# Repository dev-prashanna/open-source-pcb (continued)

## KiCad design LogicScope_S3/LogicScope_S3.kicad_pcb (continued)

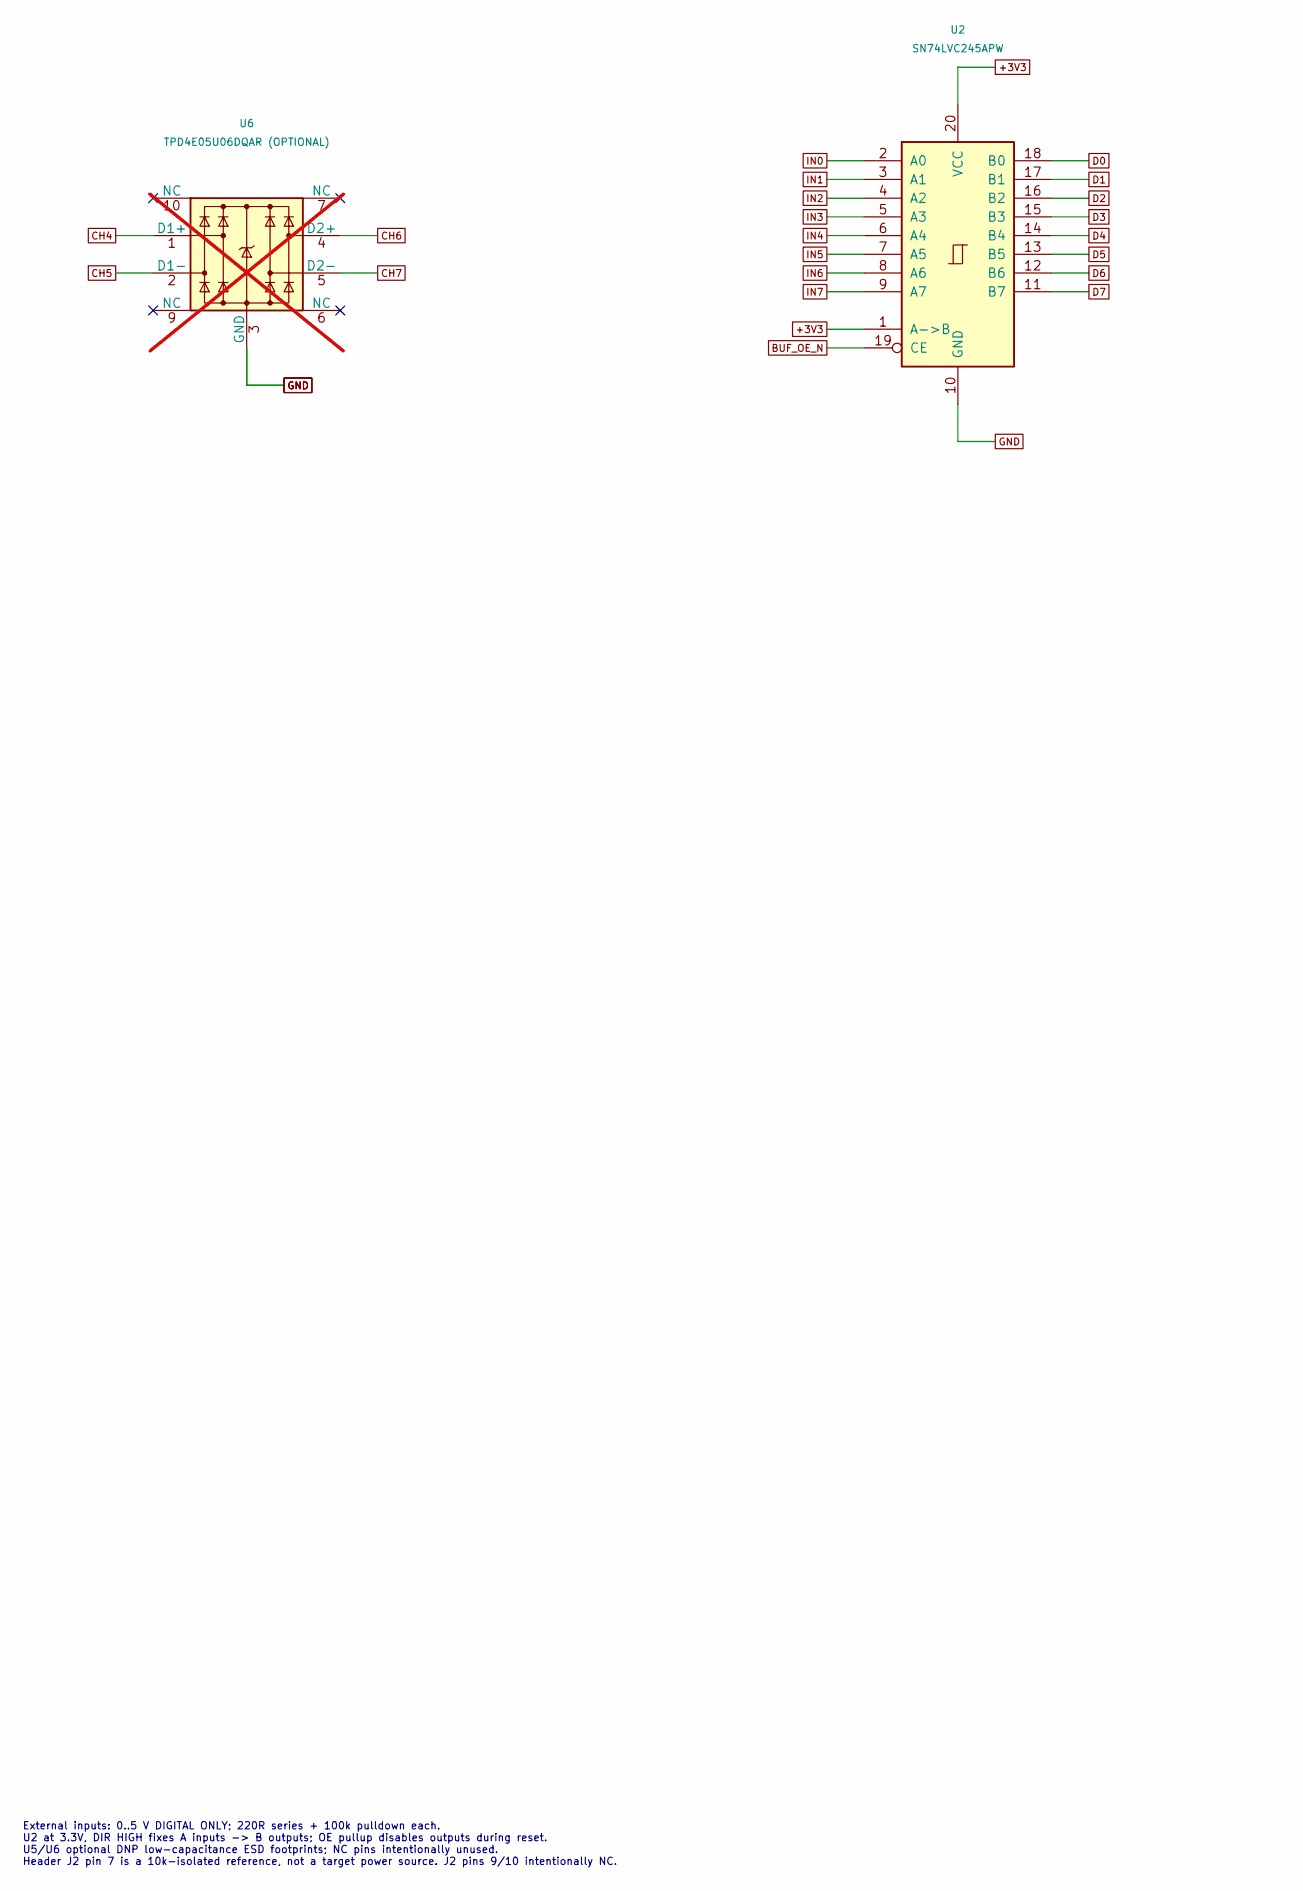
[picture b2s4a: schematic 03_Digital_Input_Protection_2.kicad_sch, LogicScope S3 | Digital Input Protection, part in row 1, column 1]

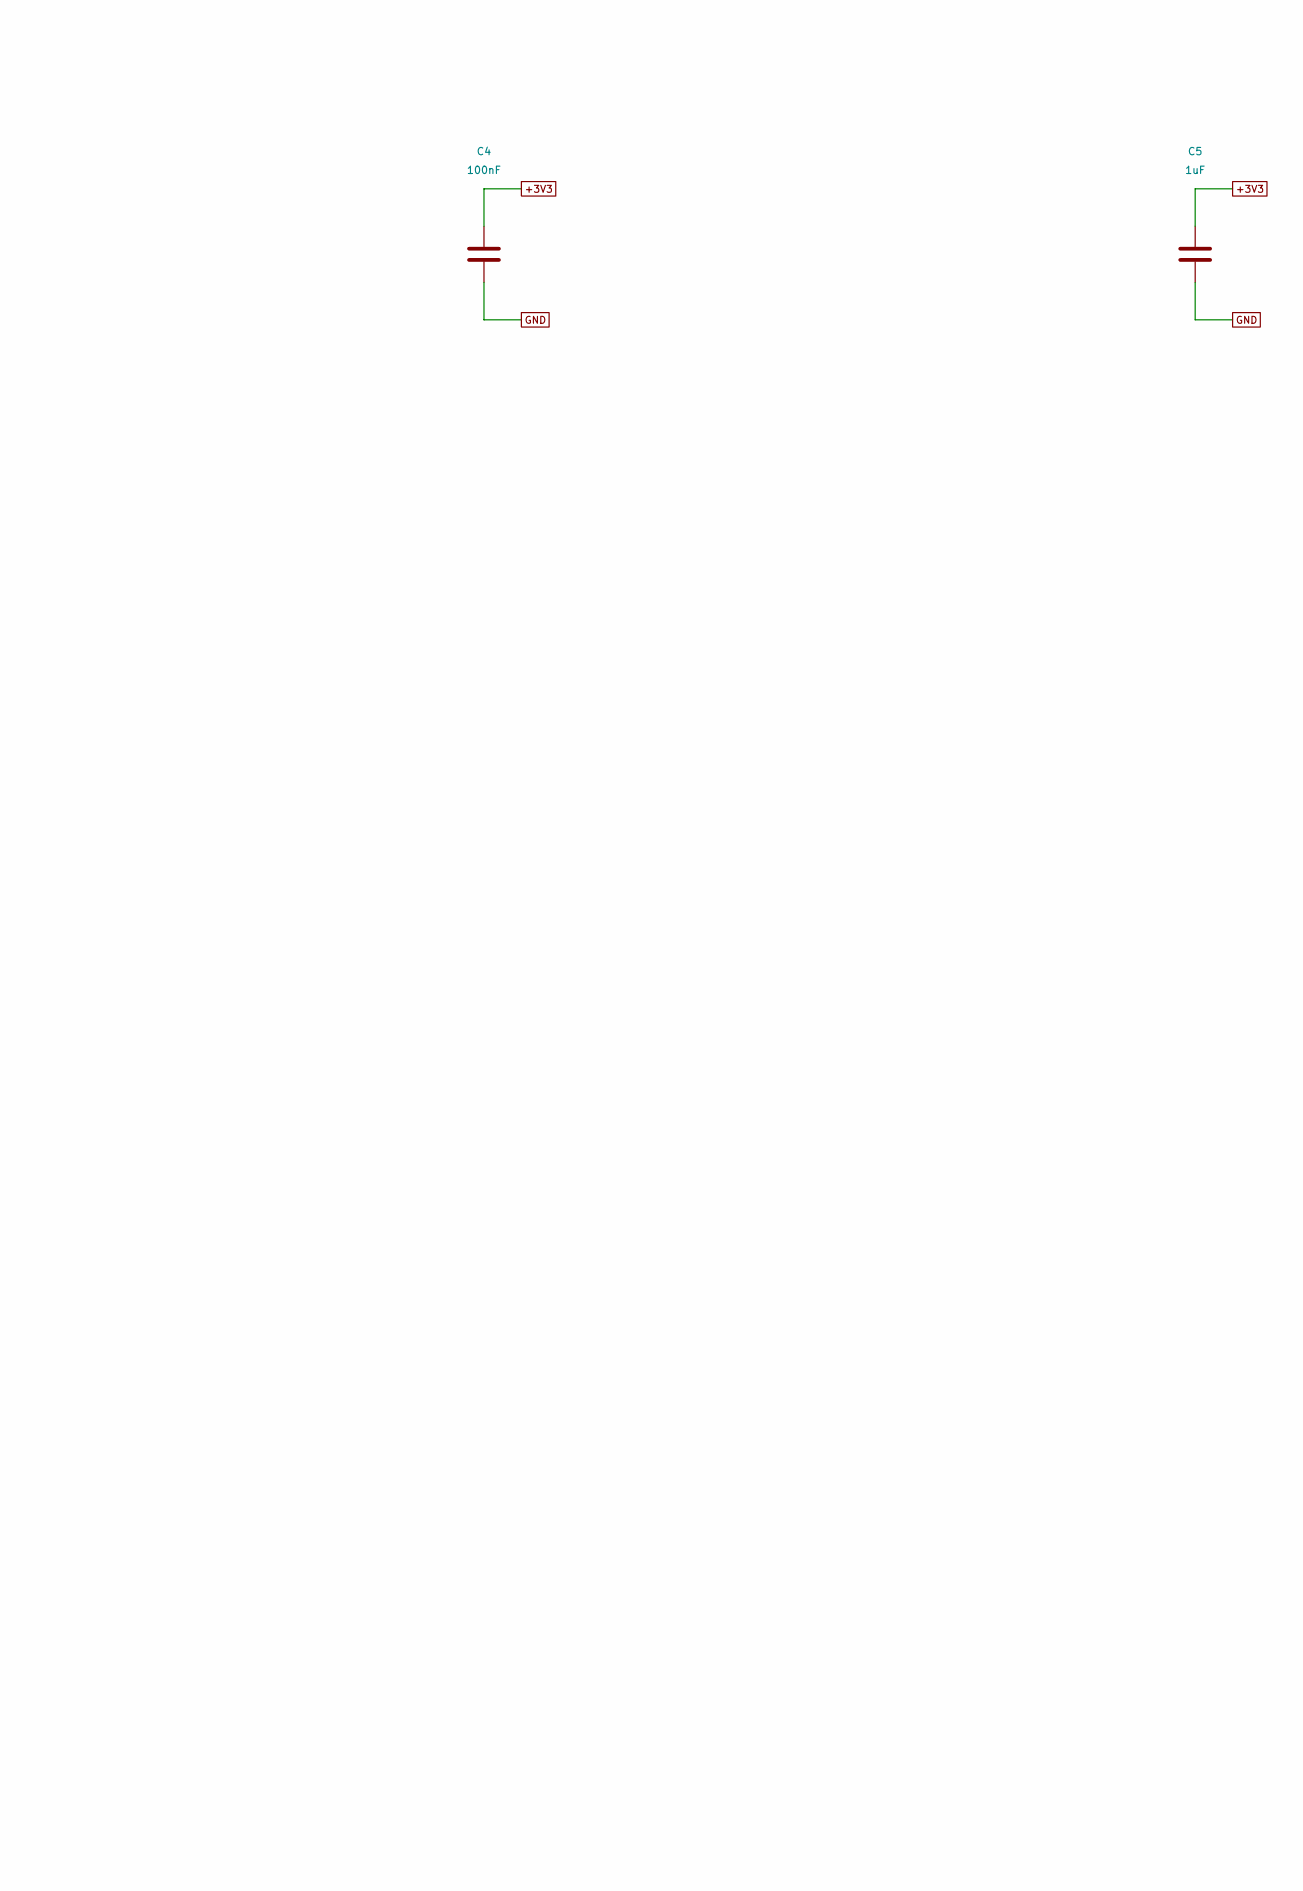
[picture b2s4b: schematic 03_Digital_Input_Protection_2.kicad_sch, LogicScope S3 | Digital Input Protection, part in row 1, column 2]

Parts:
C4: 100nF; C_0603_1608Metric; MPN GRM188R71C104KA01D
C5: 1uF; C_0603_1608Metric; MPN GRM188R61A105KA61D
U2: SN74LVC245APW; TSSOP-20_4.4x6.5mm_P0.65mm; MPN SN74LVC245APW
U6: TPD4E05U06DQAR (OPTIONAL); USON-10_2.5x1.0mm_P0.5mm; MPN TPD4E05U06DQAR; not fitted

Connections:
+3V3: C4.1, C5.1, U2.1 (A->B), U2.20 (VCC); also elsewhere on the board
BUF_OE_N: U2.19 (CE); also elsewhere on the board
CH4: U6.1 (D1+); also elsewhere on the board
CH5: U6.2 (D1-); also elsewhere on the board
CH6: U6.4 (D2+); also elsewhere on the board
CH7: U6.5 (D2-); also elsewhere on the board
D0: U2.18 (B0); also elsewhere on the board
D1: U2.17 (B1); also elsewhere on the board
D2: U2.16 (B2); also elsewhere on the board
D3: U2.15 (B3); also elsewhere on the board
D4: U2.14 (B4); also elsewhere on the board
D5: U2.13 (B5); also elsewhere on the board
D6: U2.12 (B6); also elsewhere on the board
D7: U2.11 (B7); also elsewhere on the board
GND: C4.2, C5.2, U2.10 (GND), U6.3 (GND), U6.8 (GND); also elsewhere on the board
IN0: U2.2 (A0); also elsewhere on the board
IN1: U2.3 (A1); also elsewhere on the board
IN2: U2.4 (A2); also elsewhere on the board
IN3: U2.5 (A3); also elsewhere on the board
IN4: U2.6 (A4); also elsewhere on the board
IN5: U2.7 (A5); also elsewhere on the board
IN6: U2.8 (A6); also elsewhere on the board
IN7: U2.9 (A7); also elsewhere on the board

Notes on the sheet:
External inputs: 0..5 V DIGITAL ONLY; 220R series + 100k pulldown each. U2 at 3.3V, DIR HIGH fixes A inputs -> B outputs; OE pullup disables outputs during reset. U5/U6 optional DNP low-capacitance ESD footprints; NC pins intentionally unused. Header J2 pin 7 is a 10k-isolated reference, not a targ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

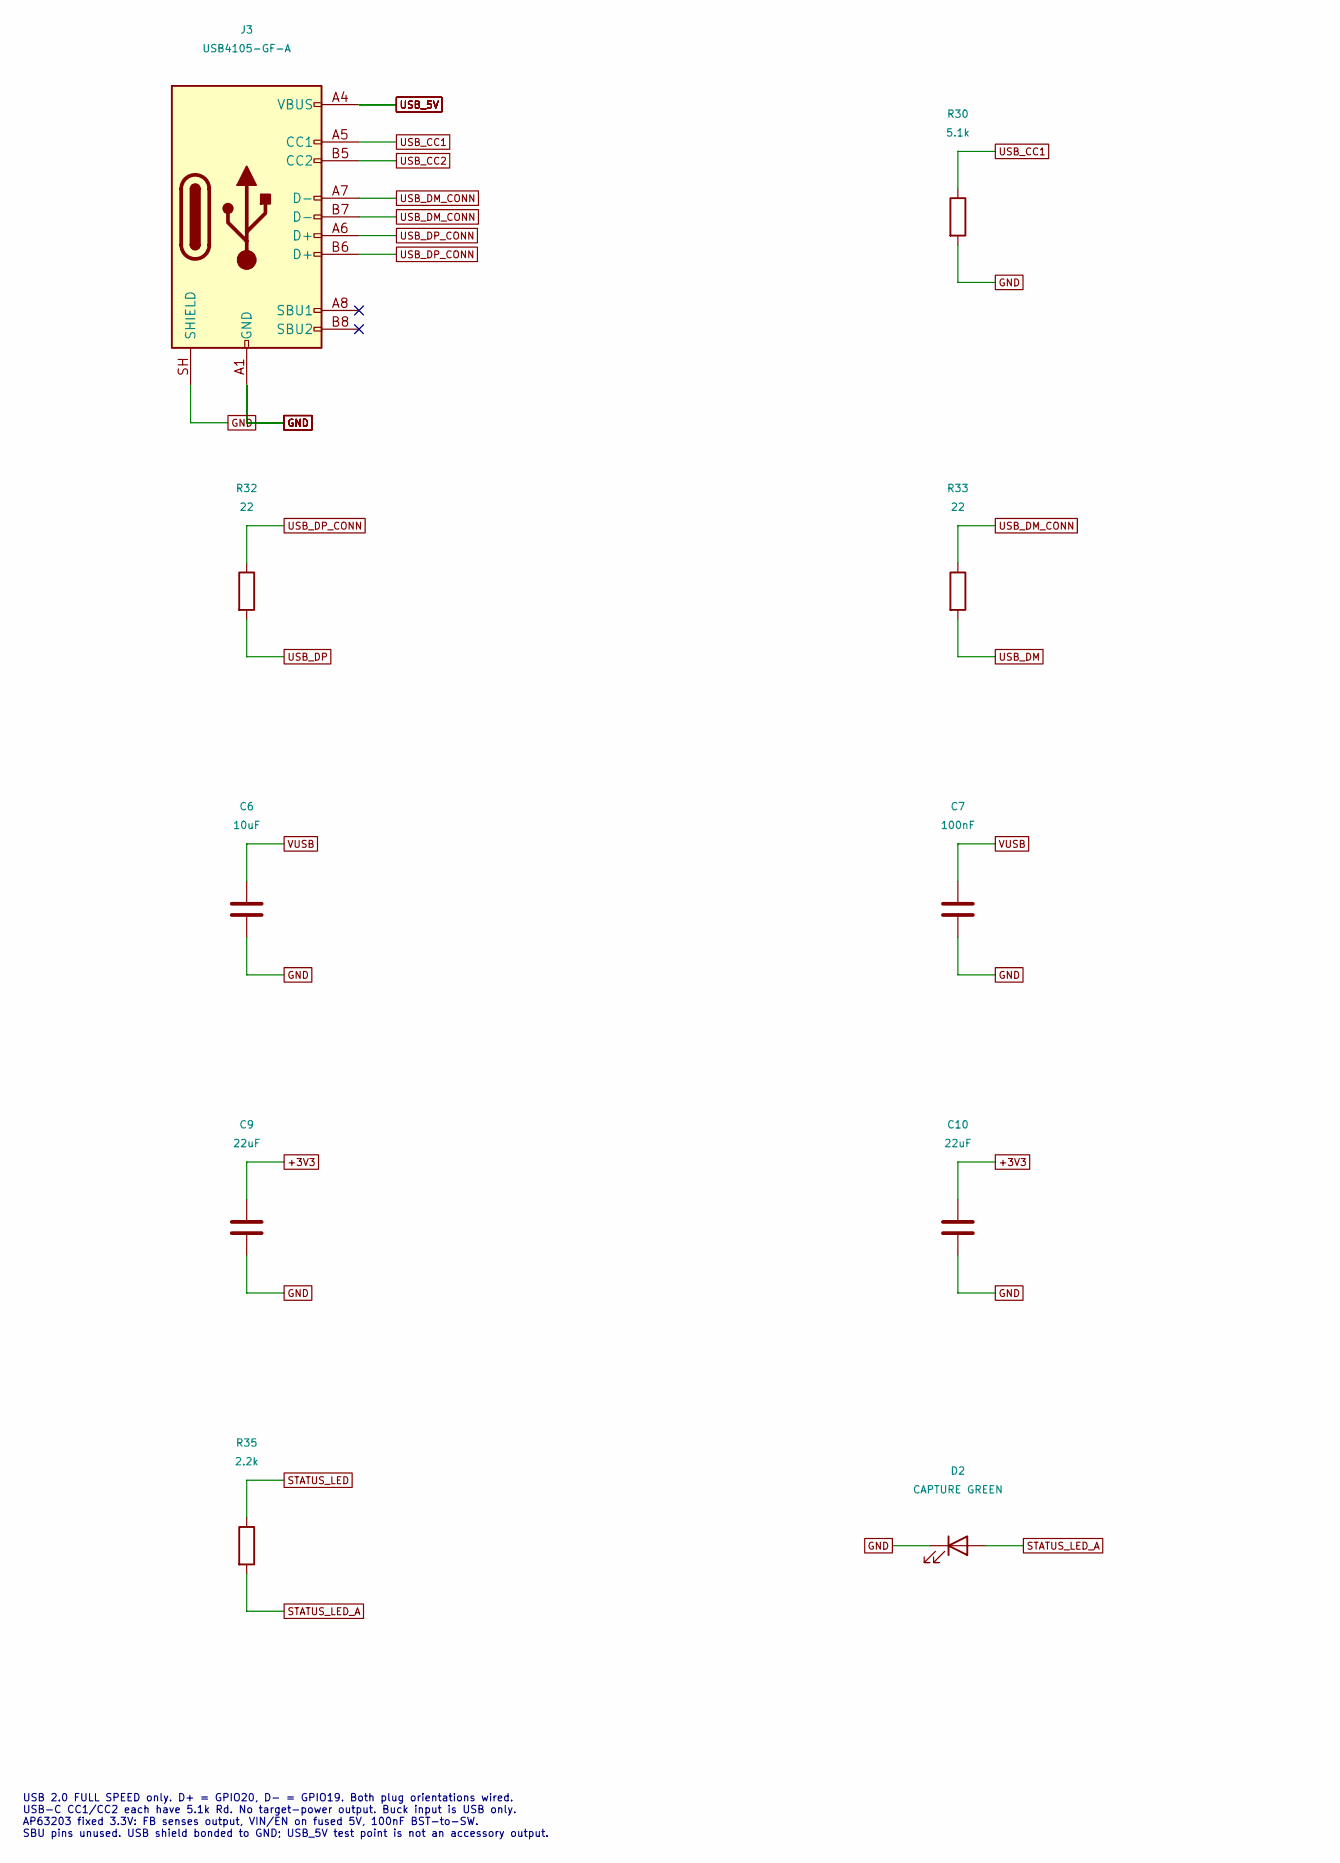
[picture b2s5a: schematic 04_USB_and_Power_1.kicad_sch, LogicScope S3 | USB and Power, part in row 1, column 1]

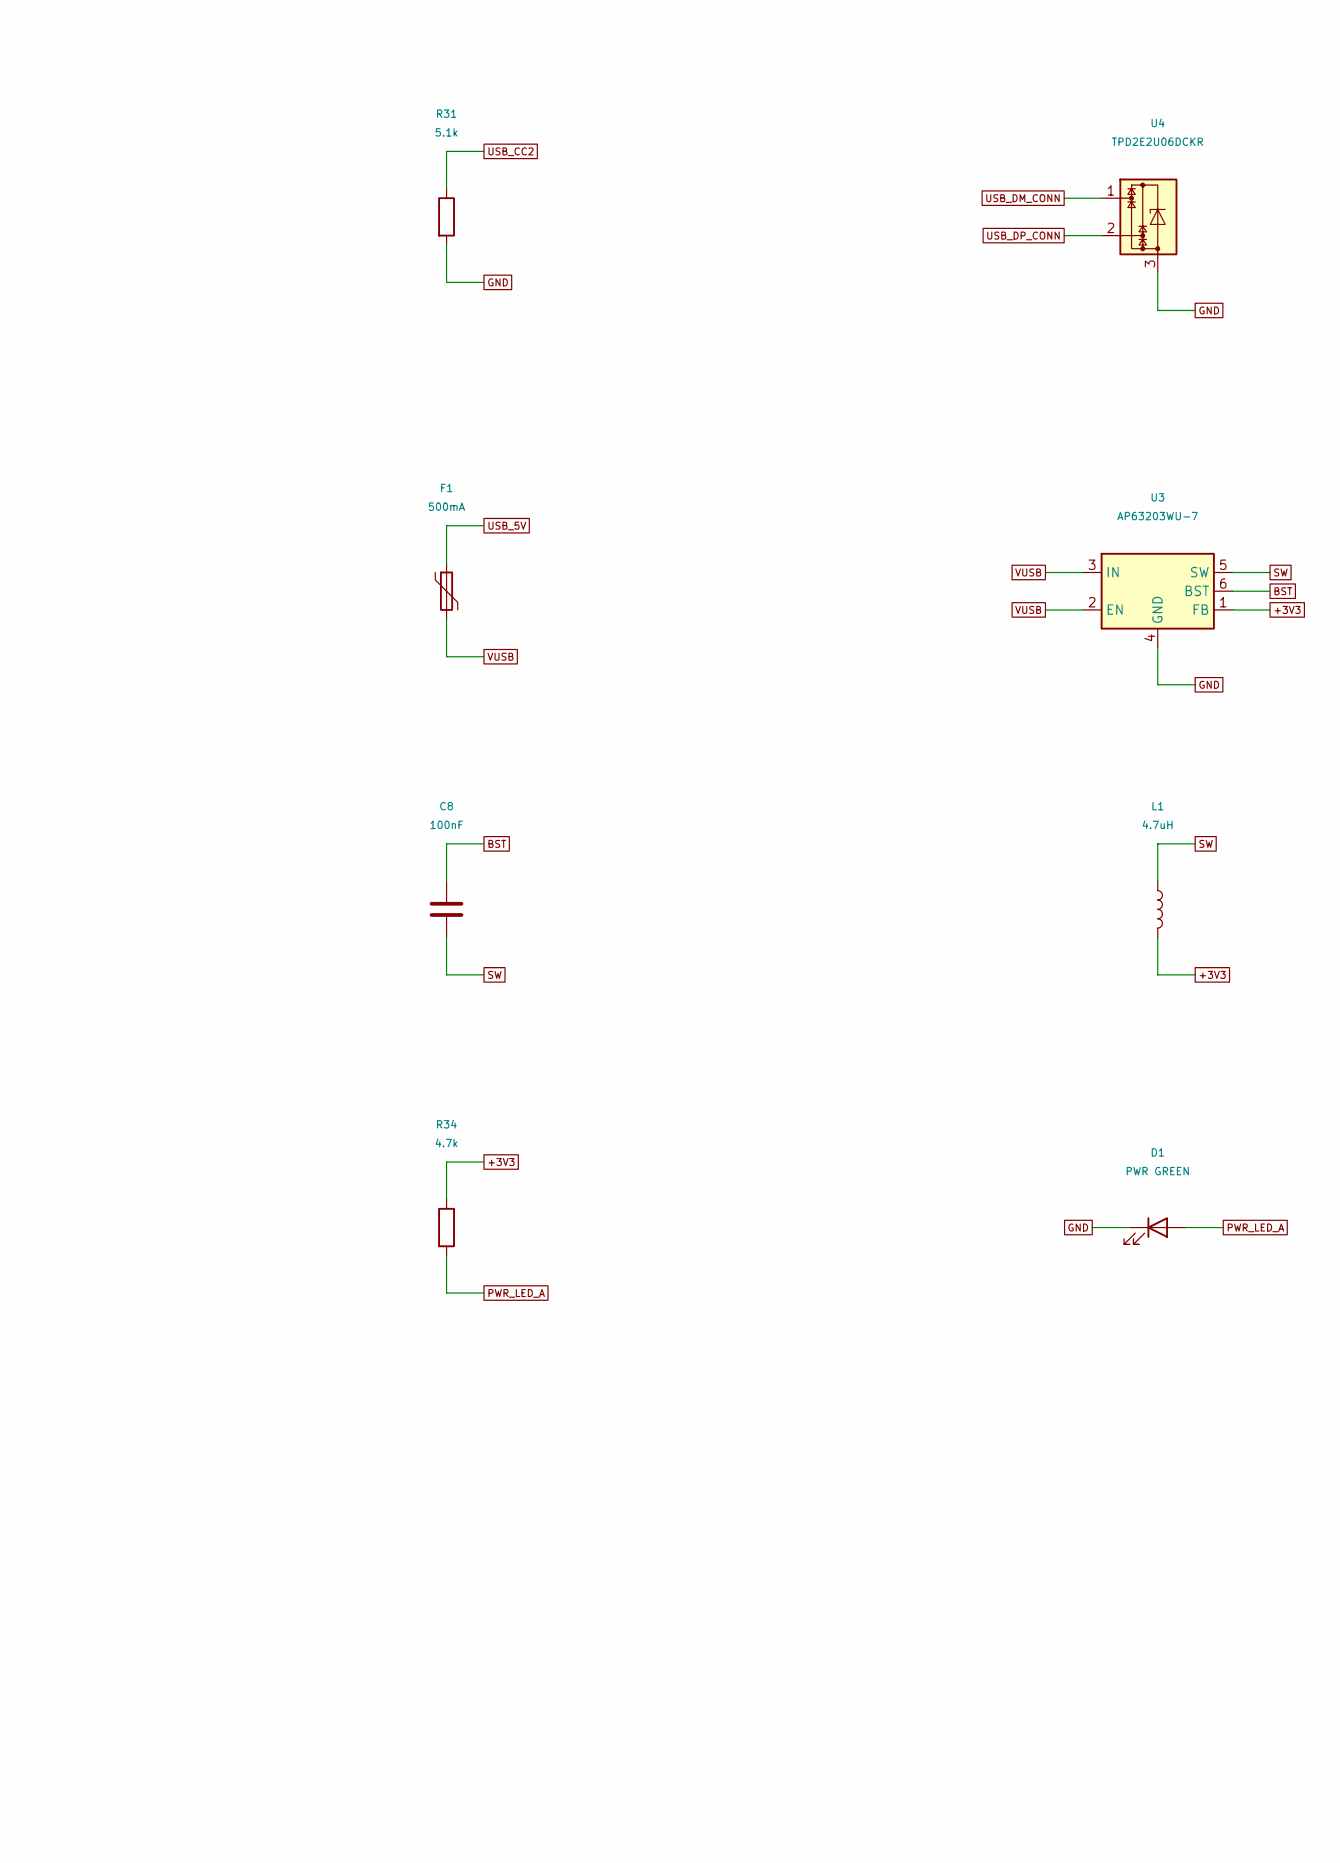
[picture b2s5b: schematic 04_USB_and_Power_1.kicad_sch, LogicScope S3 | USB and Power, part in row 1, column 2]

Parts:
C6: 10uF; C_0805_2012Metric; MPN GRM21BR61A106KE19L
C7, C8: 100nF; C_0603_1608Metric; MPN GRM188R71C104KA01D
C9, C10: 22uF; C_0805_2012Metric; MPN GRM21BR60J226ME39L
D1: PWR GREEN; LED_0603_1608Metric; MPN LTST-C190KGKT
D2: CAPTURE GREEN; LED_0603_1608Metric; MPN LTST-C190KGKT
F1: 500mA; Fuse_1206_3216Metric; MPN 1206L050YR
J3: USB4105-GF-A; USB_C_Receptacle_GCT_USB4105-xx-A_16P_TopMnt_Horizontal; MPN USB4105-GF-A
L1: 4.7uH; L_Bourns-SRN4018; MPN SRN4018-4R7M
R30, R31: 5.1k; R_0603_1608Metric; MPN RC0603FR-075K1L
R32, R33: 22; R_0402_1005Metric; MPN RC0402FR-0722RL
R34: 4.7k; R_0603_1608Metric; MPN RC0603FR-074K7L
R35: 2.2k; R_0603_1608Metric; MPN RC0603FR-072K2L
U3: AP63203WU-7; TSOT-23-6; MPN AP63203WU-7
U4: TPD2E2U06DCKR; SOT-323_SC-70; MPN TPD2E2U06DCKR

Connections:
+3V3: C9.1, C10.1, L1.2, R34.1, U3.1 (FB); also elsewhere on the board
BST: C8.1, U3.6 (BST)
GND: C6.2, C7.2, C9.2, C10.2, D1.1 (K), D2.1 (K), J3.A1 (GND), J3.A12 (GND), J3.B1 (GND), J3.B12 (GND), J3.SH (SHIELD), R30.2, R31.2, U3.4 (GND), U4.3; also elsewhere on the board
PWR_LED_A: D1.2 (A), R34.2
STATUS_LED: R35.1; also elsewhere on the board
STATUS_LED_A: D2.2 (A), R35.2
SW: C8.2, L1.1, U3.5 (SW)
USB_5V: F1.1, J3.A4 (VBUS), J3.A9 (VBUS), J3.B4 (VBUS), J3.B9 (VBUS); also elsewhere on the board
USB_CC1: J3.A5 (CC1), R30.1
USB_CC2: J3.B5 (CC2), R31.1
USB_DM: R33.2; also elsewhere on the board
USB_DM_CONN: J3.A7 (D-), J3.B7 (D-), R33.1, U4.1
USB_DP: R32.2; also elsewhere on the board
USB_DP_CONN: J3.A6 (D+), J3.B6 (D+), R32.1, U4.2
VUSB: C6.1, C7.1, F1.2, U3.2 (EN), U3.3 (IN); also elsewhere on the board

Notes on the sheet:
USB 2.0 FULL SPEED only. D+ = GPIO20, D- = GPIO19. Both plug orientations wired. USB-C CC1/CC2 each have 5.1k Rd. No target-power output. Buck input is USB only. AP63203 fixed 3.3V: FB senses output, VIN/EN on fused 5V, 100nF BST-to-SW. SBU pins unused. USB shield bonded to GND; USB_5V test point i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

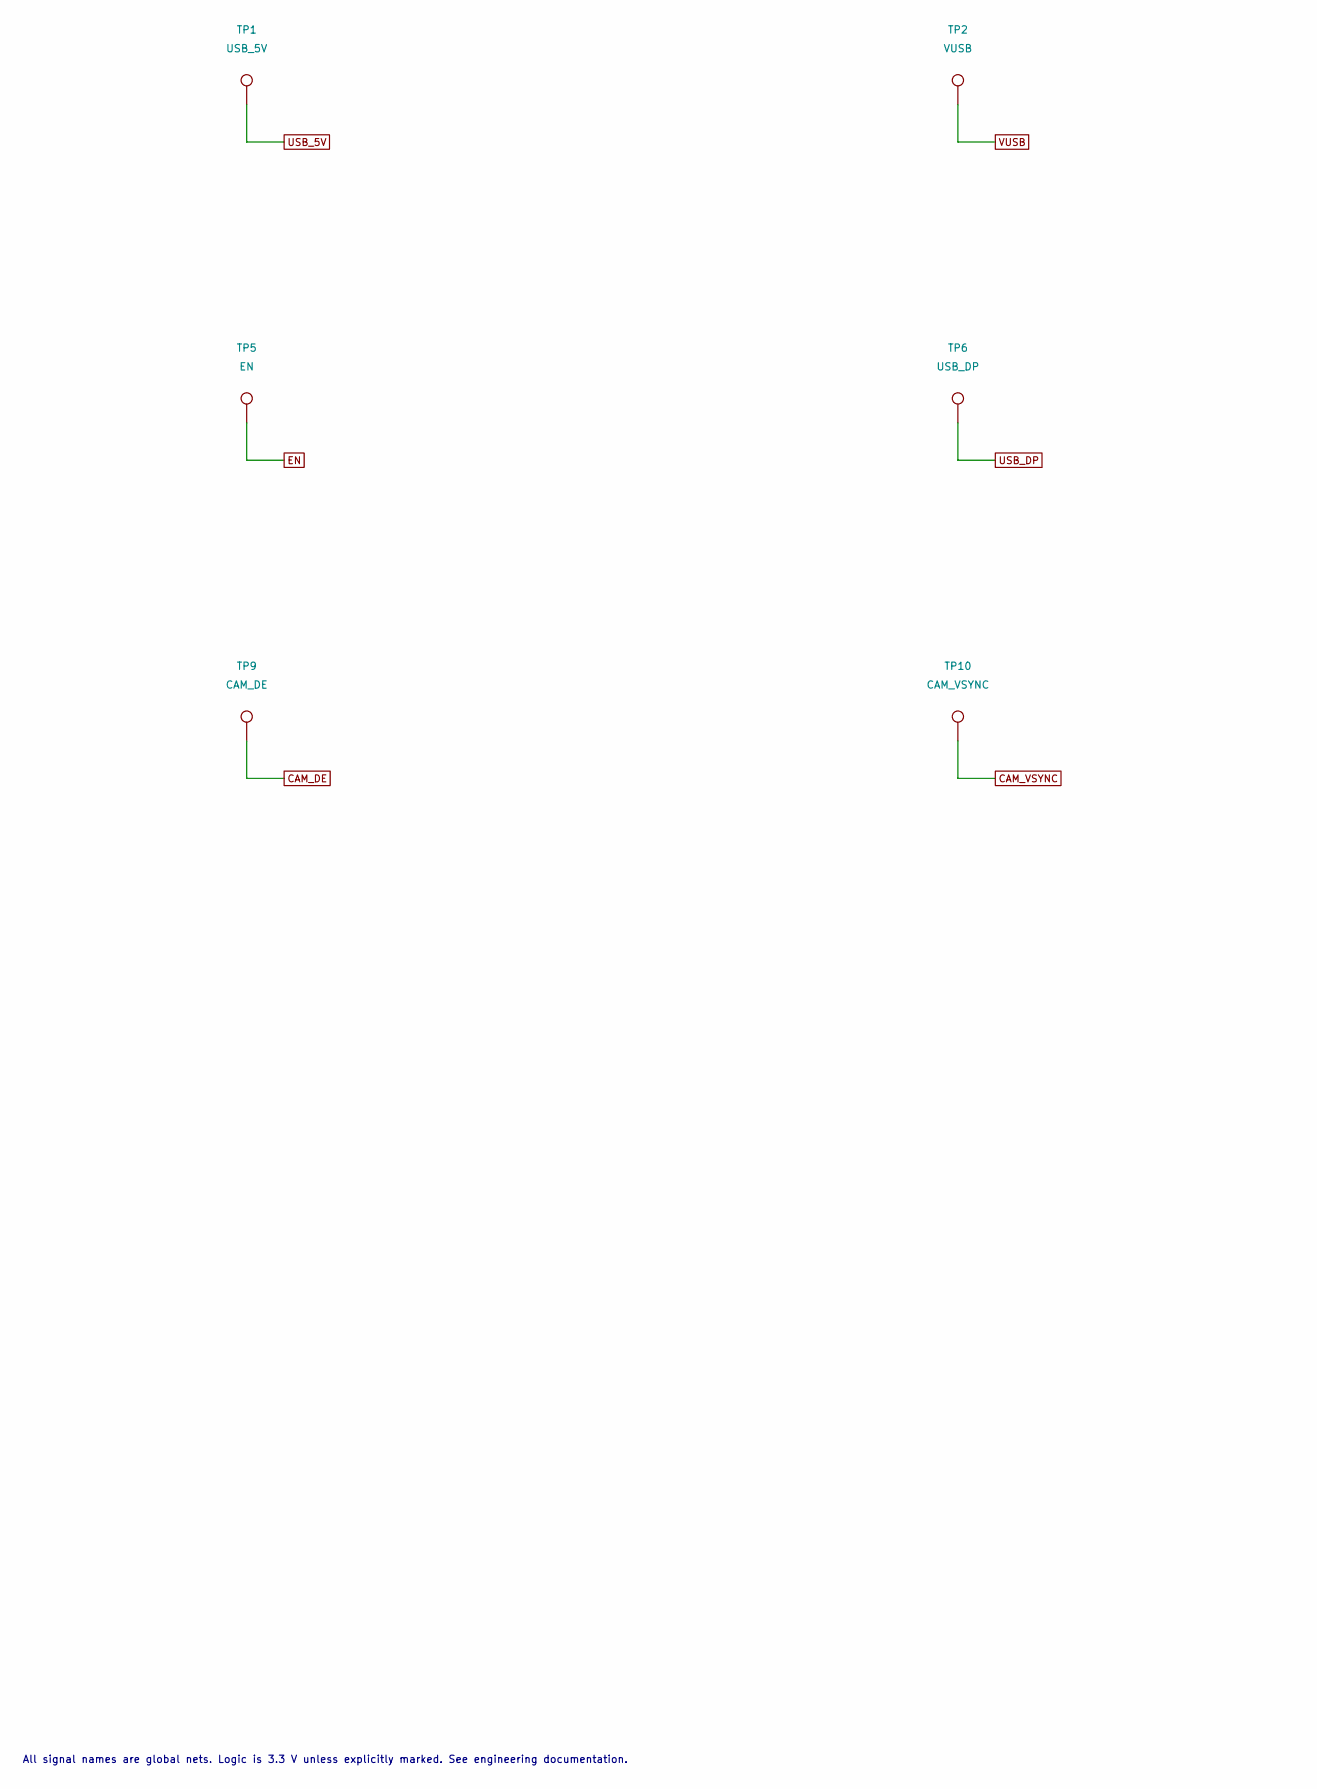
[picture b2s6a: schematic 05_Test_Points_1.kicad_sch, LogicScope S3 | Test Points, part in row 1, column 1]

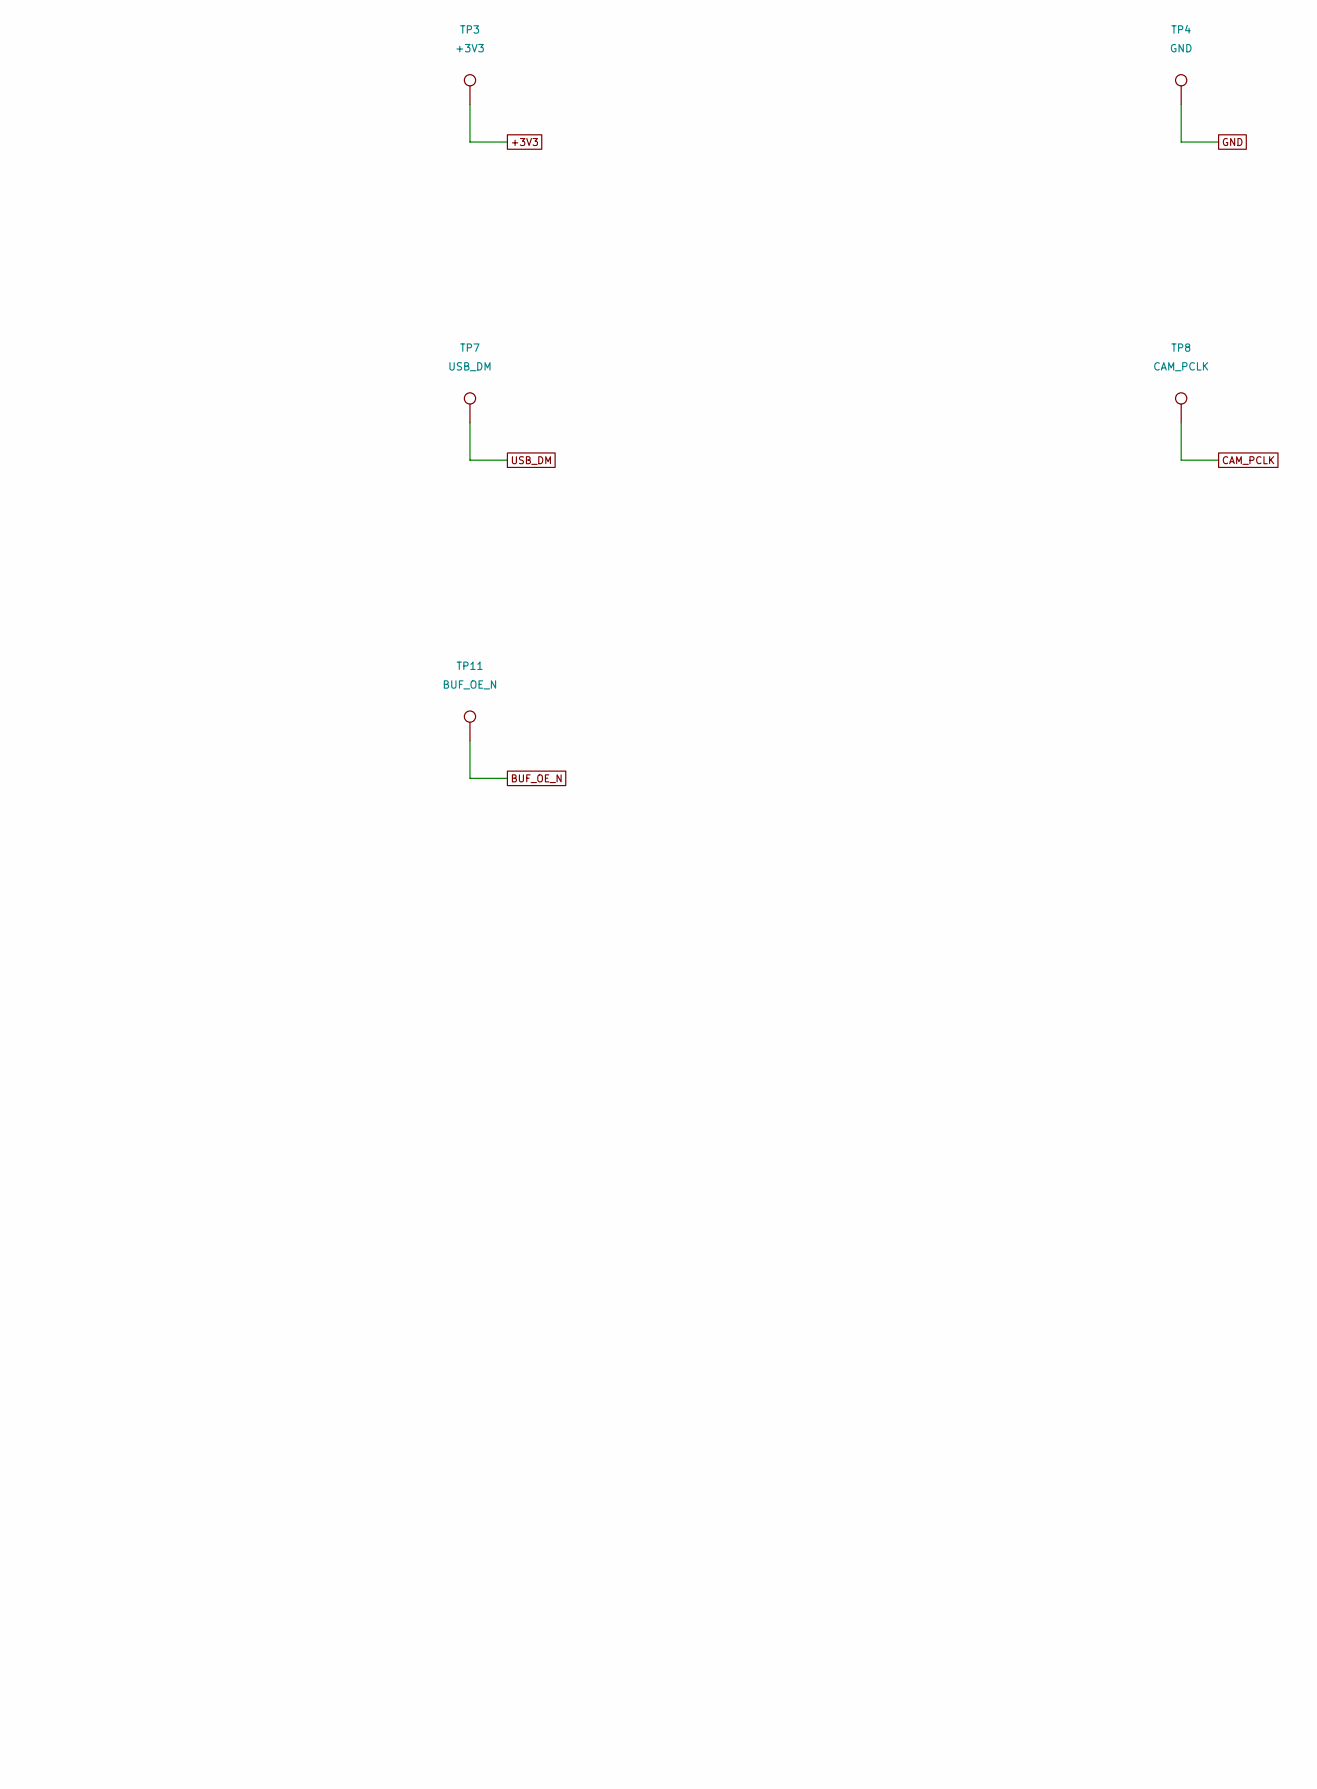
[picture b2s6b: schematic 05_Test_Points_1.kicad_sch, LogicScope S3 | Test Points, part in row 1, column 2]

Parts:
TP1: USB_5V; TestPoint_Pad_D1.0mm; MPN PCB_PAD
TP2: VUSB; TestPoint_Pad_D1.0mm; MPN PCB_PAD
TP3: +3V3; TestPoint_Pad_D1.0mm; MPN PCB_PAD
TP4: GND; TestPoint_Pad_D1.0mm; MPN PCB_PAD
TP5: EN; TestPoint_Pad_D1.0mm; MPN PCB_PAD
TP6: USB_DP; TestPoint_D0.5mm; MPN PCB_PAD
TP7: USB_DM; TestPoint_D0.5mm; MPN PCB_PAD
TP8: CAM_PCLK; TestPoint_Pad_D1.0mm; MPN PCB_PAD
TP9: CAM_DE; TestPoint_Pad_D1.0mm; MPN PCB_PAD
TP10: CAM_VSYNC; TestPoint_Pad_D1.0mm; MPN PCB_PAD
TP11: BUF_OE_N; TestPoint_Pad_D1.0mm; MPN PCB_PAD

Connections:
+3V3: TP3.1; also elsewhere on the board
BUF_OE_N: TP11.1; also elsewhere on the board
CAM_DE: TP9.1; also elsewhere on the board
CAM_PCLK: TP8.1; also elsewhere on the board
CAM_VSYNC: TP10.1; also elsewhere on the board
EN: TP5.1; also elsewhere on the board
GND: TP4.1; also elsewhere on the board
USB_5V: TP1.1; also elsewhere on the board
USB_DM: TP7.1; also elsewhere on the board
USB_DP: TP6.1; also elsewhere on the board
VUSB: TP2.1; also elsewhere on the board

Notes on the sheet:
All signal names are global nets. Logic is 3.3 V unless explicitly marked. See engineering documentation.

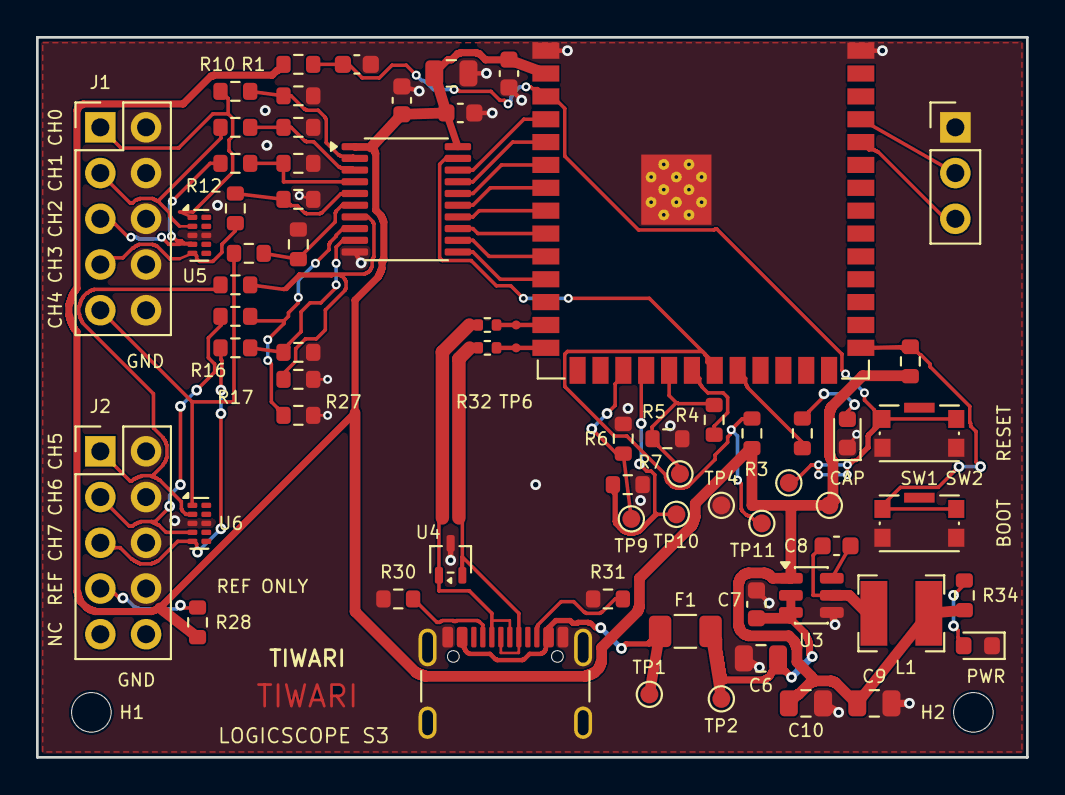
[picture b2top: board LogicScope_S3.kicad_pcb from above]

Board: 2 copper layers, 55.0 x 40.0 mm, 69 parts (0 on the bottom side), 49 nets.

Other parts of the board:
H1, H2: MountingHole_2.2mm_M2

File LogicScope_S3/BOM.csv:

Reference,Value,MPN,Manufacturer,Footprint,DNP,Datasheet
U1,ESP32-S3-WROOM-1-N8R2,ESP32-S3-WROOM-1-N8R2,Espressif,LogicScope:ESP32-S3-WROOM-1_Overhang,NO,https://documentation.espressif.com/esp32-s3-wroom-1_wroom-1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
C1,100nF,GRM188R71C104KA01D,Murata,Capacitor_SMD:C_0603_1608Metric,NO,https://www.murata.com/en-global/products/capacitor/ceramicc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
C2,10uF,GRM21BR61A106KE19L,Murata,Capacitor_SMD:C_0805_2012Metric,NO,https://www.murata.com/en-global/products/capacitor/ceramicc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
R1,10k,RC0603FR-0710KL,Yageo,Resistor_SMD:R_0603_1608Metric,NO,https://www.yageo.com/en/Product/Index/rchip
C3,1uF,GRM188R61A105KA61D,Murata,Capacitor_SMD:C_0603_1608Metric,NO,https://www.murata.com/en-global/products/capacitor/ceramicc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
R2,10k,RC0603FR-0710KL,Yageo,Resistor_SMD:R_0603_1608Metric,NO,https://www.yageo.com/en/Product/Index/rchip
R3,10k,RC0603FR-0710KL,Yageo,Resistor_SMD:R_0603_1608Metric,NO,https://www.yageo.com/en/Product/Index/rchip
R4,33,RC0603FR-0733RL,Yageo,Resistor_SMD:R_0603_1608Metric,NO,https://www.yageo.com/en/Product/Index/rchip
R5,100k,RC0603FR-07100KL,Yageo,Resistor_SMD:R_0603_1608Metric,NO,https://www.yageo.com/en/Product/Index/rchip
R6,100k,RC0603FR-07100KL,Yageo,Resistor_SMD:R_0603_1608Metric,NO,https://www.yageo.com/en/Product/Index/rchip
R7,100k,RC0603FR-07100KL,Yageo,Resistor_SMD:R_0603_1608Metric,NO,https://www.yageo.com/en/Product/Index/rchip
SW1,RESET,KMR221GLFS,C&K,Button_Switch_SMD:SW_Push_1P1T-SH_NO_CK_KMR2xxG,NO,https://www.ckswitches.com/media/1464/kmr2.pdf
SW2,BOOT,KMR221GLFS,C&K,Button_Switch_SMD:SW_Push_1P1T-SH_NO_CK_KMR2xxG,NO,https://www.ckswitches.com/media/1464/kmr2.pdf
J4,DEBUG 3V3 UART,61300311121,Wurth Elektronik,Connector_PinHeader_2.54mm:PinHeader_1x03_P2.54mm_Vertical,NO,https://www.we-online.com/en/components/products/WR-PHD_254M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
J1,CH0..4 + GROUNDS,61301021121,Wurth Elektronik,Connector_PinHeader_2.54mm:PinHeader_2x05_P2.54mm_Vertical,NO,https://www.we-online.com/en/components/products/WR-PHD_254M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
J2,CH5..7 / REF ONLY,61301021121,Wurth Elektronik,Connector_PinHeader_2.54mm:PinHeader_2x05_P2.54mm_Vertical,NO,https://www.we-online.com/en/components/products/WR-PHD_254M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
R10,220,RC0603FR-07220RL,Yageo,Resistor_SMD:R_0603_1608Metric,NO,https://www.yageo.com/en/Product/Index/rchip
R20,100k,RC0603FR-07100KL,Yageo,Resistor_SMD:R_0603_1608Metric,NO,https://www.yageo.com/en/Product/Index/rchip
R11,220,RC0603FR-07220RL,Yageo,Resistor_SMD:R_0603_1608Metric,NO,https://www.yageo.com/en/Product/Index/rchip
R21,100k,RC0603FR-07100KL,Yageo,Resistor_SMD:R_0603_1608Metric,NO,https://www.yageo.com/en/Product/Index/rchip
R12,220,RC0603FR-07220RL,Yageo,Resistor_SMD:R_0603_1608Metric,NO,https://www.yageo.com/en/Product/Index/rchip
R22,100k,RC0603FR-07100KL,Yageo,Resistor_SMD:R_0603_1608Metric,NO,https://www.yageo.com/en/Product/Index/rchip
R13,220,RC0603FR-07220RL,Yageo,Resistor_SMD:R_0603_1608Metric,NO,https://www.yageo.com/en/Product/Index/rchip
R23,100k,RC0603FR-07100KL,Yageo,Resistor_SMD:R_0603_1608Metric,NO,https://www.yageo.com/en/Product/Index/rchip
R14,220,RC0603FR-07220RL,Yageo,Resistor_SMD:R_0603_1608Metric,NO,https://www.yageo.com/en/Product/Index/rchip
R24,100k,RC0603FR-07100KL,Yageo,Resistor_SMD:R_0603_1608Metric,NO,https://www.yageo.com/en/Product/Index/rchip
R15,220,RC0603FR-07220RL,Yageo,Resistor_SMD:R_0603_1608Metric,NO,https://www.yageo.com/en/Product/Index/rchip
R25,100k,RC0603FR-07100KL,Yageo,Resistor_SMD:R_0603_1608Metric,NO,https://www.yageo.com/en/Product/Index/rchip
R16,220,RC0603FR-07220RL,Yageo,Resistor_SMD:R_0603_1608Metric,NO,https://www.yageo.com/en/Product/Index/rchip
R26,100k,RC0603FR-07100KL,Yageo,Resistor_SMD:R_0603_1608Metric,NO,https://www.yageo.com/en/Product/Index/rchip
R17,220,RC0603FR-07220RL,Yageo,Resistor_SMD:R_0603_1608Metric,NO,https://www.yageo.com/en/Product/Index/rchip
R27,100k,RC0603FR-07100KL,Yageo,Resistor_SMD:R_0603_1608Metric,NO,https://www.yageo.com/en/Product/Index/rchip
R28,10k,RC0603FR-0710KL,Yageo,Resistor_SMD:R_0603_1608Metric,NO,https://www.yageo.com/en/Product/Index/rchip
U5,TPD4E05U06DQAR (OPTIONAL),TPD4E05U06DQAR,Texas Instruments,Package_SON:USON-10_2.5x1.0mm_P0.5mm,YES,https://www.ti.com/lit/ds/symlink/tpd4e05u06.pdf
U6,TPD4E05U06DQAR (OPTIONAL),TPD4E05U06DQAR,Texas Instruments,Package_SON:USON-10_2.5x1.0mm_P0.5mm,YES,https://www.ti.com/lit/ds/symlink/tpd4e05u06.pdf
U2,SN74LVC245APW,SN74LVC245APW,Texas Instruments,Package_SO:TSSOP-20_4.4x6.5mm_P0.65mm,NO,https://www.ti.com/lit/ds/symlink/sn74lvc245a.pdf
C4,100nF,GRM188R71C104KA01D,Murata,Capacitor_SMD:C_0603_1608Metric,NO,https://www.murata.com/en-global/products/capacitor/ceramicc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
C5,1uF,GRM188R61A105KA61D,Murata,Capacitor_SMD:C_0603_1608Metric,NO,https://www.murata.com/en-global/products/capacitor/ceramicc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
J3,USB4105-GF-A,USB4105-GF-A,GCT,Connector_USB:USB_C_Receptacle_GCT_USB4105-xx-A_16P_TopMnt_Horizontal,NO,https://gct.co/connector/usb4105
R30,5.1k,RC0603FR-075K1L,Yageo,Resistor_SMD:R_0603_1608Metric,NO,https://www.yageo.com/en/Product/Index/rchip
R31,5.1k,RC0603FR-075K1L,Yageo,Resistor_SMD:R_0603_1608Metric,NO,https://www.yageo.com/en/Product/Index/rchip
U4,TPD2E2U06DCKR,TPD2E2U06DCKR,Texas Instruments,Package_TO_SOT_SMD:SOT-323_SC-70,NO,https://www.ti.com/lit/ds/symlink/tpd2e2u06.pdf
R32,22,RC0402FR-0722RL,Yageo,Resistor_SMD:R_0402_1005Metric,NO,https://www.yageo.com/en/Product/Index/rchip
R33,22,RC0402FR-0722RL,Yageo,Resistor_SMD:R_0402_1005Metric,NO,https://www.yageo.com/en/Product/Index/rchip
F1,500mA,1206L050YR,Littelfuse,Fuse:Fuse_1206_3216Metric,NO,https://www.littelfuse.com/products/polyswitch-resettable-pp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
U3,AP63203WU-7,AP63203WU-7,Diodes Incorporated,Package_TO_SOT_SMD:TSOT-23-6,NO,https://www.diodes.com/assets/Datasheets/AP63200-AP63201-AP6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
C6,10uF,GRM21BR61A106KE19L,Murata,Capacitor_SMD:C_0805_2012Metric,NO,https://www.murata.com/en-global/products/capacitor/ceramicc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
C7,100nF,GRM188R71C104KA01D,Murata,Capacitor_SMD:C_0603_1608Metric,NO,https://www.murata.com/en-global/products/capacitor/ceramicc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
C8,100nF,GRM188R71C104KA01D,Murata,Capacitor_SMD:C_0603_1608Metric,NO,https://www.murata.com/en-global/products/capacitor/ceramicc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
L1,4.7uH,SRN4018-4R7M,Bourns,Inductor_SMD:L_Bourns-SRN4018,NO,https://www.bourns.com/docs/product-datasheets/srn4018.pdf
C9,22uF,GRM21BR60J226ME39L,Murata,Capacitor_SMD:C_0805_2012Metric,NO,https://www.murata.com/en-global/products/capacitor/ceramicc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
C10,22uF,GRM21BR60J226ME39L,Murata,Capacitor_SMD:C_0805_2012Metric,NO,https://www.murata.com/en-global/products/capacitor/ceramicc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
R34,4.7k,RC0603FR-074K7L,Yageo,Resistor_SMD:R_0603_1608Metric,NO,https://www.yageo.com/en/Product/Index/rchip
D1,PWR GREEN,LTST-C190KGKT,Lite-On,LED_SMD:LED_0603_1608Metric,NO,
R35,2.2k,RC0603FR-072K2L,Yageo,Resistor_SMD:R_0603_1608Metric,NO,https://www.yageo.com/en/Product/Index/rchip
D2,CAPTURE GREEN,LTST-C190KGKT,Lite-On,LED_SMD:LED_0603_1608Metric,NO,
